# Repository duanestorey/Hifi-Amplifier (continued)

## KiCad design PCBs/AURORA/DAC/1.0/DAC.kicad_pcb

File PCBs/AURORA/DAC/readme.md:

## DAC 

### Version History

- 1.0: Initial Release

## #Speciality Components

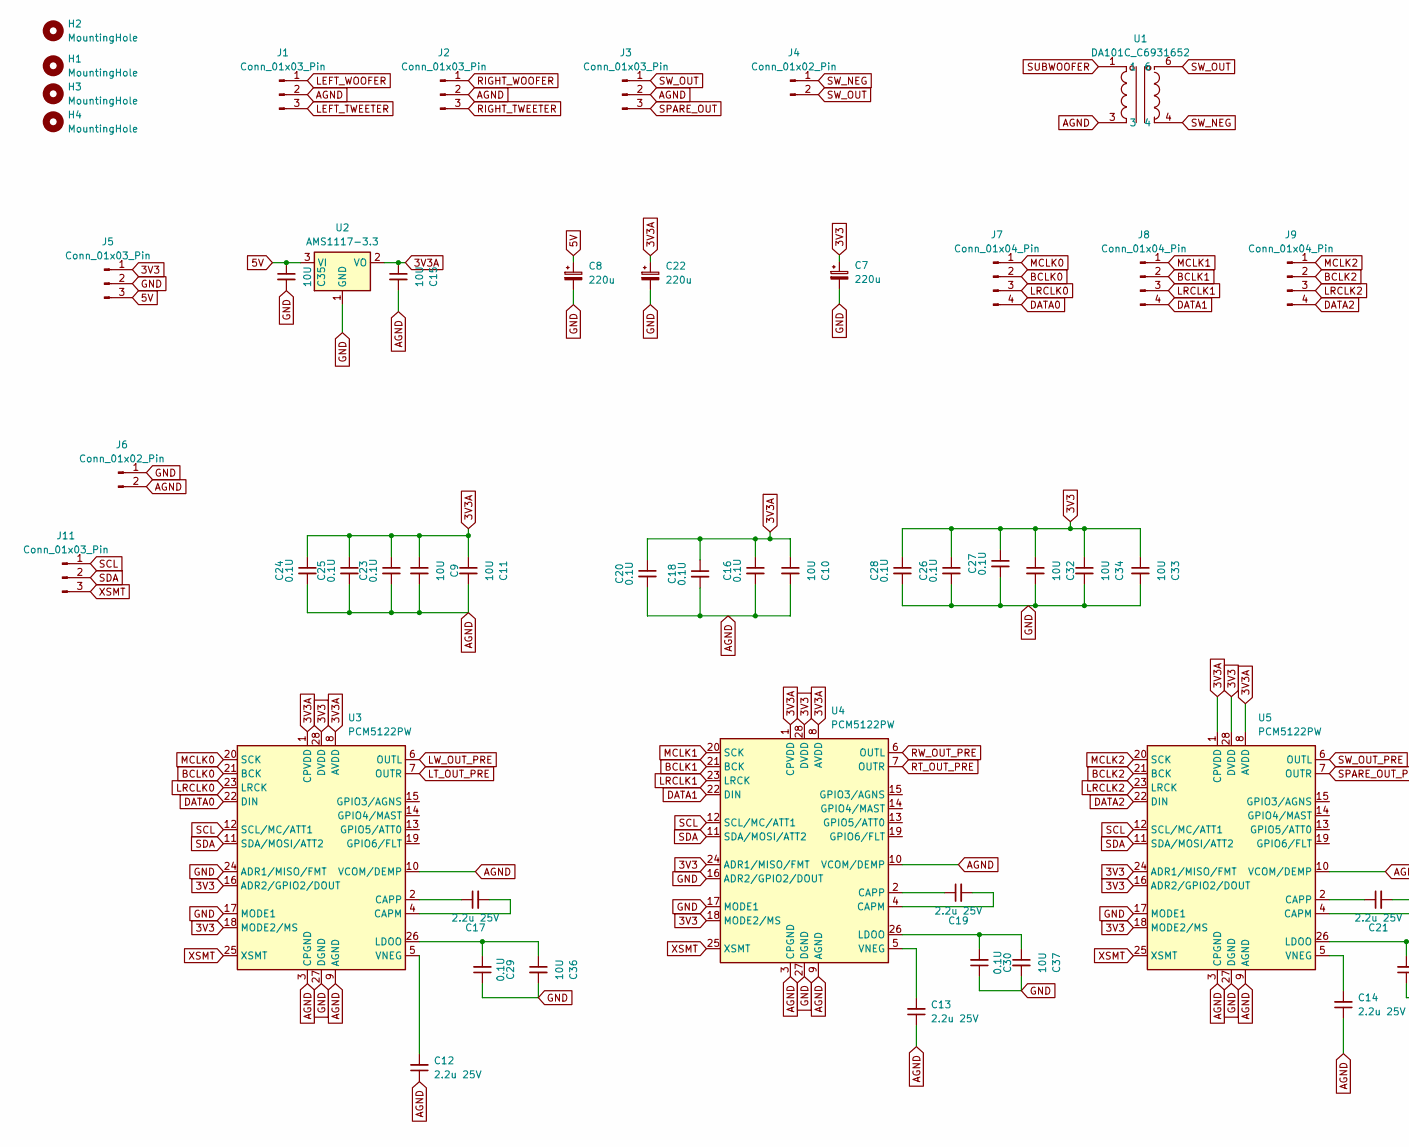
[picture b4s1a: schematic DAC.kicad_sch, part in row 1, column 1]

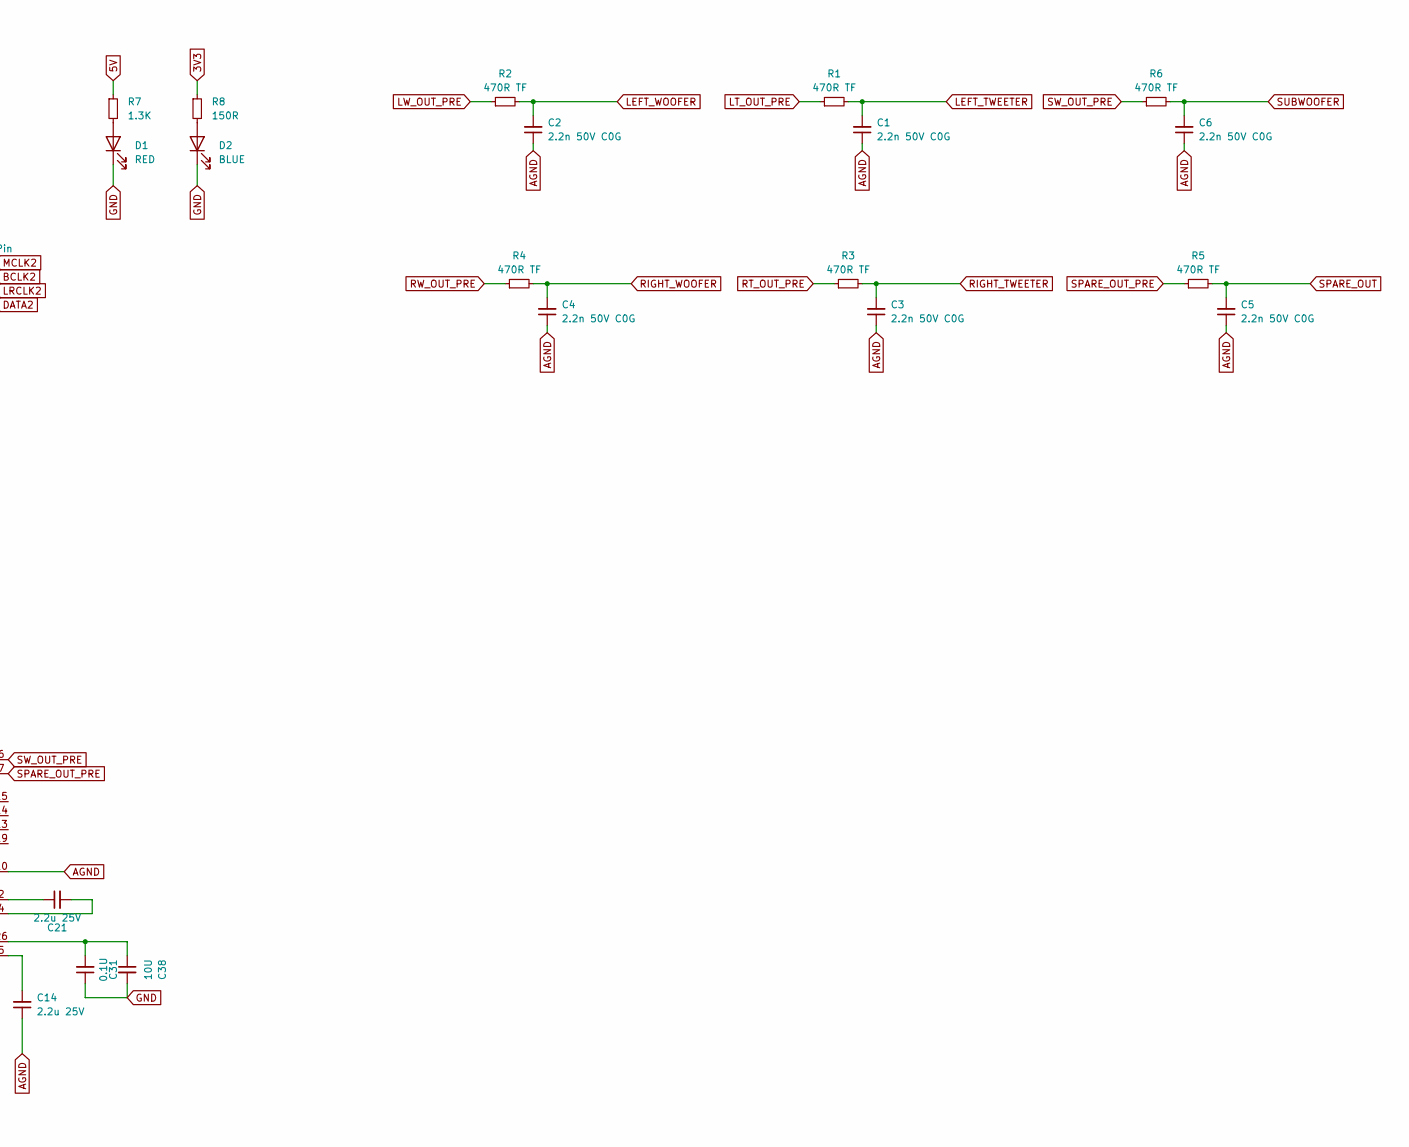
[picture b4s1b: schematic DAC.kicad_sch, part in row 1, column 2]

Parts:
C1, C2, C3, C4: 2.2n 50V C0G; C_0805_2012Metric_Pad1.18x1.45mm_HandSolder; Mouser 791-0805N222F500CT
C5, C6: 2.2n 50V C0G; C_0805_2012Metric_Pad1.18x1.45mm_HandSolder
C7, C8, C22: 220u; CP_Radial_D6.3mm_P2.50mm
C9, C10, C11, C15, C32, C33, C34, C35, C36, C37, C38: 10U; C_1206_3216Metric_Pad1.33x1.80mm_HandSolder
C12, C13, C14: 2.2u 25V; C_1206_3216Metric_Pad1.33x1.80mm_HandSolder
C16, C18, C20, C23, C24, C25, C26, C27, C28, C29, C30, C31: 0.1U; C_0805_2012Metric_Pad1.18x1.45mm_HandSolder
C17, C19, C21: 2.2u 25V; C_0805_2012Metric_Pad1.18x1.45mm_HandSolder
D1: RED; LED_0603_1608Metric
D2: BLUE; LED_0603_1608Metric
H1, H2, H3, H4: MountingHole; MountingHole_3.2mm_M3_DIN965_Pad_TopOnly
J1, J2, J3, J5, J11: Conn_01x03_Pin; JST_PH_B3B-PH-K_1x03_P2.00mm_Vertical
J4: Conn_01x02_Pin; JST_PH_B2B-PH-K_1x02_P2.00mm_Vertical
J6: Conn_01x02_Pin; PinHeader_1x02_P2.54mm_Vertical
J7, J8, J9: Conn_01x04_Pin; JST_PH_B4B-PH-K_1x04_P2.00mm_Vertical
R1, R2, R3, R4, R5, R6: 470R TF; R_0805_2012Metric_Pad1.20x1.40mm_HandSolder; Mouser 603-RT0805FRE07470RL
R7: 1.3K; R_0603_1608Metric_Pad0.98x0.95mm_HandSolder
R8: 150R; R_0603_1608Metric_Pad0.98x0.95mm_HandSolder
U1: DA101C_C6931652; XFMR-TH_4P-L9.5-W9.0-P5.08-LS10.2_C9900096976; LCSC Part C6931652
U2: AMS1117-3.3; SOT-223-3_TabPin2
U3, U4, U5: PCM5122PW; TSSOP-28_4.4x9.7mm_P0.65mm; Mouser 595-PCM5142PWR

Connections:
3V3: C7.1, C26.1, C27.1, C28.1, C32.1, C33.1, C34.1, J5.1, R8.1, U3.16 (ADR2/GPIO2/DOUT), U3.18 (MODE2/MS), U3.28 (DVDD), U4.18 (MODE2/MS), U4.24 (ADR1/MISO/FMT), U4.28 (DVDD), U5.16 (ADR2/GPIO2/DOUT), U5.18 (MODE2/MS), U5.24 (ADR1/MISO/FMT), U5.28 (DVDD)
3V3A: C9.1, C10.1, C11.1, C15.1, C16.1, C18.1, C20.1, C22.1, C23.1, C24.1, C25.1, U2.2 (VO), U3.1 (CPVDD), U3.8 (AVDD), U4.1 (CPVDD), U4.8 (AVDD), U5.1 (CPVDD), U5.8 (AVDD)
5V: C8.1, C35.1, J5.3, R7.1, U2.3 (VI)
AGND: C1.1, C2.1, C3.1, C4.1, C5.1, C6.1, C9.2, C10.2, C11.2, C12.1, C13.1, C14.1, C15.2, C16.2, C18.2, C20.2, C23.2, C24.2, C25.2, J1.2, J2.2, J3.2, J6.2, U1.3, U3.3 (CPGND), U3.9 (AGND), U3.10 (VCOM/DEMP), U4.3 (CPGND), U4.9 (AGND), U4.10 (VCOM/DEMP), U5.3 (CPGND), U5.9 (AGND), U5.10 (VCOM/DEMP)
BCLK0: J7.2, U3.21 (BCK)
BCLK1: J8.2, U4.21 (BCK)
BCLK2: J9.2, U5.21 (BCK)
DATA0: J7.4, U3.22 (DIN)
DATA1: J8.4, U4.22 (DIN)
DATA2: J9.4, U5.22 (DIN)
GND: C7.2, C8.2, C22.2, C26.2, C27.2, C28.2, C29.1, C30.1, C31.1, C32.2, C33.2, C34.2, C35.2, C36.2, C37.2, C38.2, D1.1 (K), D2.1 (K), J5.2, J6.1, U2.1 (GND), U3.17 (MODE1), U3.24 (ADR1/MISO/FMT), U3.27 (DGND), U4.16 (ADR2/GPIO2/DOUT), U4.17 (MODE1), U4.27 (DGND), U5.17 (MODE1), U5.27 (DGND)
LEFT_TWEETER: C1.2, J1.3, R1.2
LEFT_WOOFER: C2.2, J1.1, R2.2
LRCLK0: J7.3, U3.23 (LRCK)
LRCLK1: J8.3, U4.23 (LRCK)
LRCLK2: J9.3, U5.23 (LRCK)
LT_OUT_PRE: R1.1, U3.7 (OUTR)
LW_OUT_PRE: R2.1, U3.6 (OUTL)
MCLK0: J7.1, U3.20 (SCK)
MCLK1: J8.1, U4.20 (SCK)
MCLK2: J9.1, U5.20 (SCK)
unnamed: D1.2 (A), R7.2
unnamed: D2.2 (A), R8.2
unnamed: C17.2, U3.4 (CAPM)
unnamed: C17.1, U3.2 (CAPP)
unnamed: C29.2, C36.1, U3.26 (LDOO)
unnamed: C12.2, U3.5 (VNEG)
unnamed: C19.2, U4.4 (CAPM)
unnamed: C19.1, U4.2 (CAPP)
unnamed: C30.2, C37.1, U4.26 (LDOO)
unnamed: C13.2, U4.5 (VNEG)
unnamed: C21.2, U5.4 (CAPM)
unnamed: C21.1, U5.2 (CAPP)
unnamed: C31.2, C38.1, U5.26 (LDOO)
unnamed: C14.2, U5.5 (VNEG)
RIGHT_TWEETER: C3.2, J2.3, R3.2
RIGHT_WOOFER: C4.2, J2.1, R4.2
RT_OUT_PRE: R3.1, U4.7 (OUTR)
RW_OUT_PRE: R4.1, U4.6 (OUTL)
SCL: J11.1, U3.12 (SCL/MC/ATT1), U4.12 (SCL/MC/ATT1), U5.12 (SCL/MC/ATT1)
SDA: J11.2, U3.11 (SDA/MOSI/ATT2), U4.11 (SDA/MOSI/ATT2), U5.11 (SDA/MOSI/ATT2)
SPARE_OUT: C5.2, J3.3, R5.2
SPARE_OUT_PRE: R5.1, U5.7 (OUTR)
SUBWOOFER: C6.2, R6.2, U1.1
SW_NEG: J4.1, U1.4
SW_OUT: J3.1, J4.2, U1.6
SW_OUT_PRE: R6.1, U5.6 (OUTL)
XSMT: J11.3, U3.25 (XSMT), U4.25 (XSMT), U5.25 (XSMT)

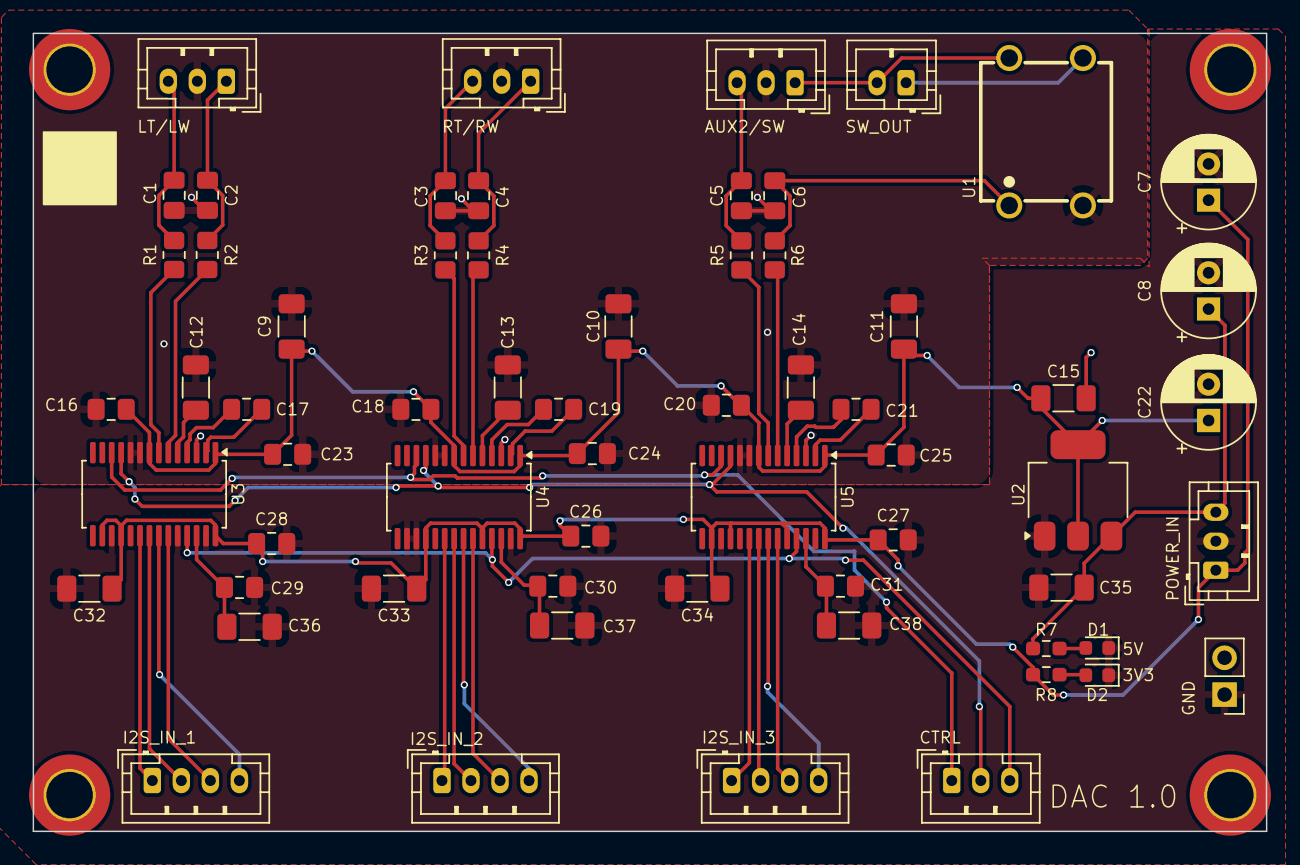
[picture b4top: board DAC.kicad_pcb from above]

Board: 2 copper layers, 85.0 x 55.0 mm, 67 parts (0 on the bottom side), 48 nets.

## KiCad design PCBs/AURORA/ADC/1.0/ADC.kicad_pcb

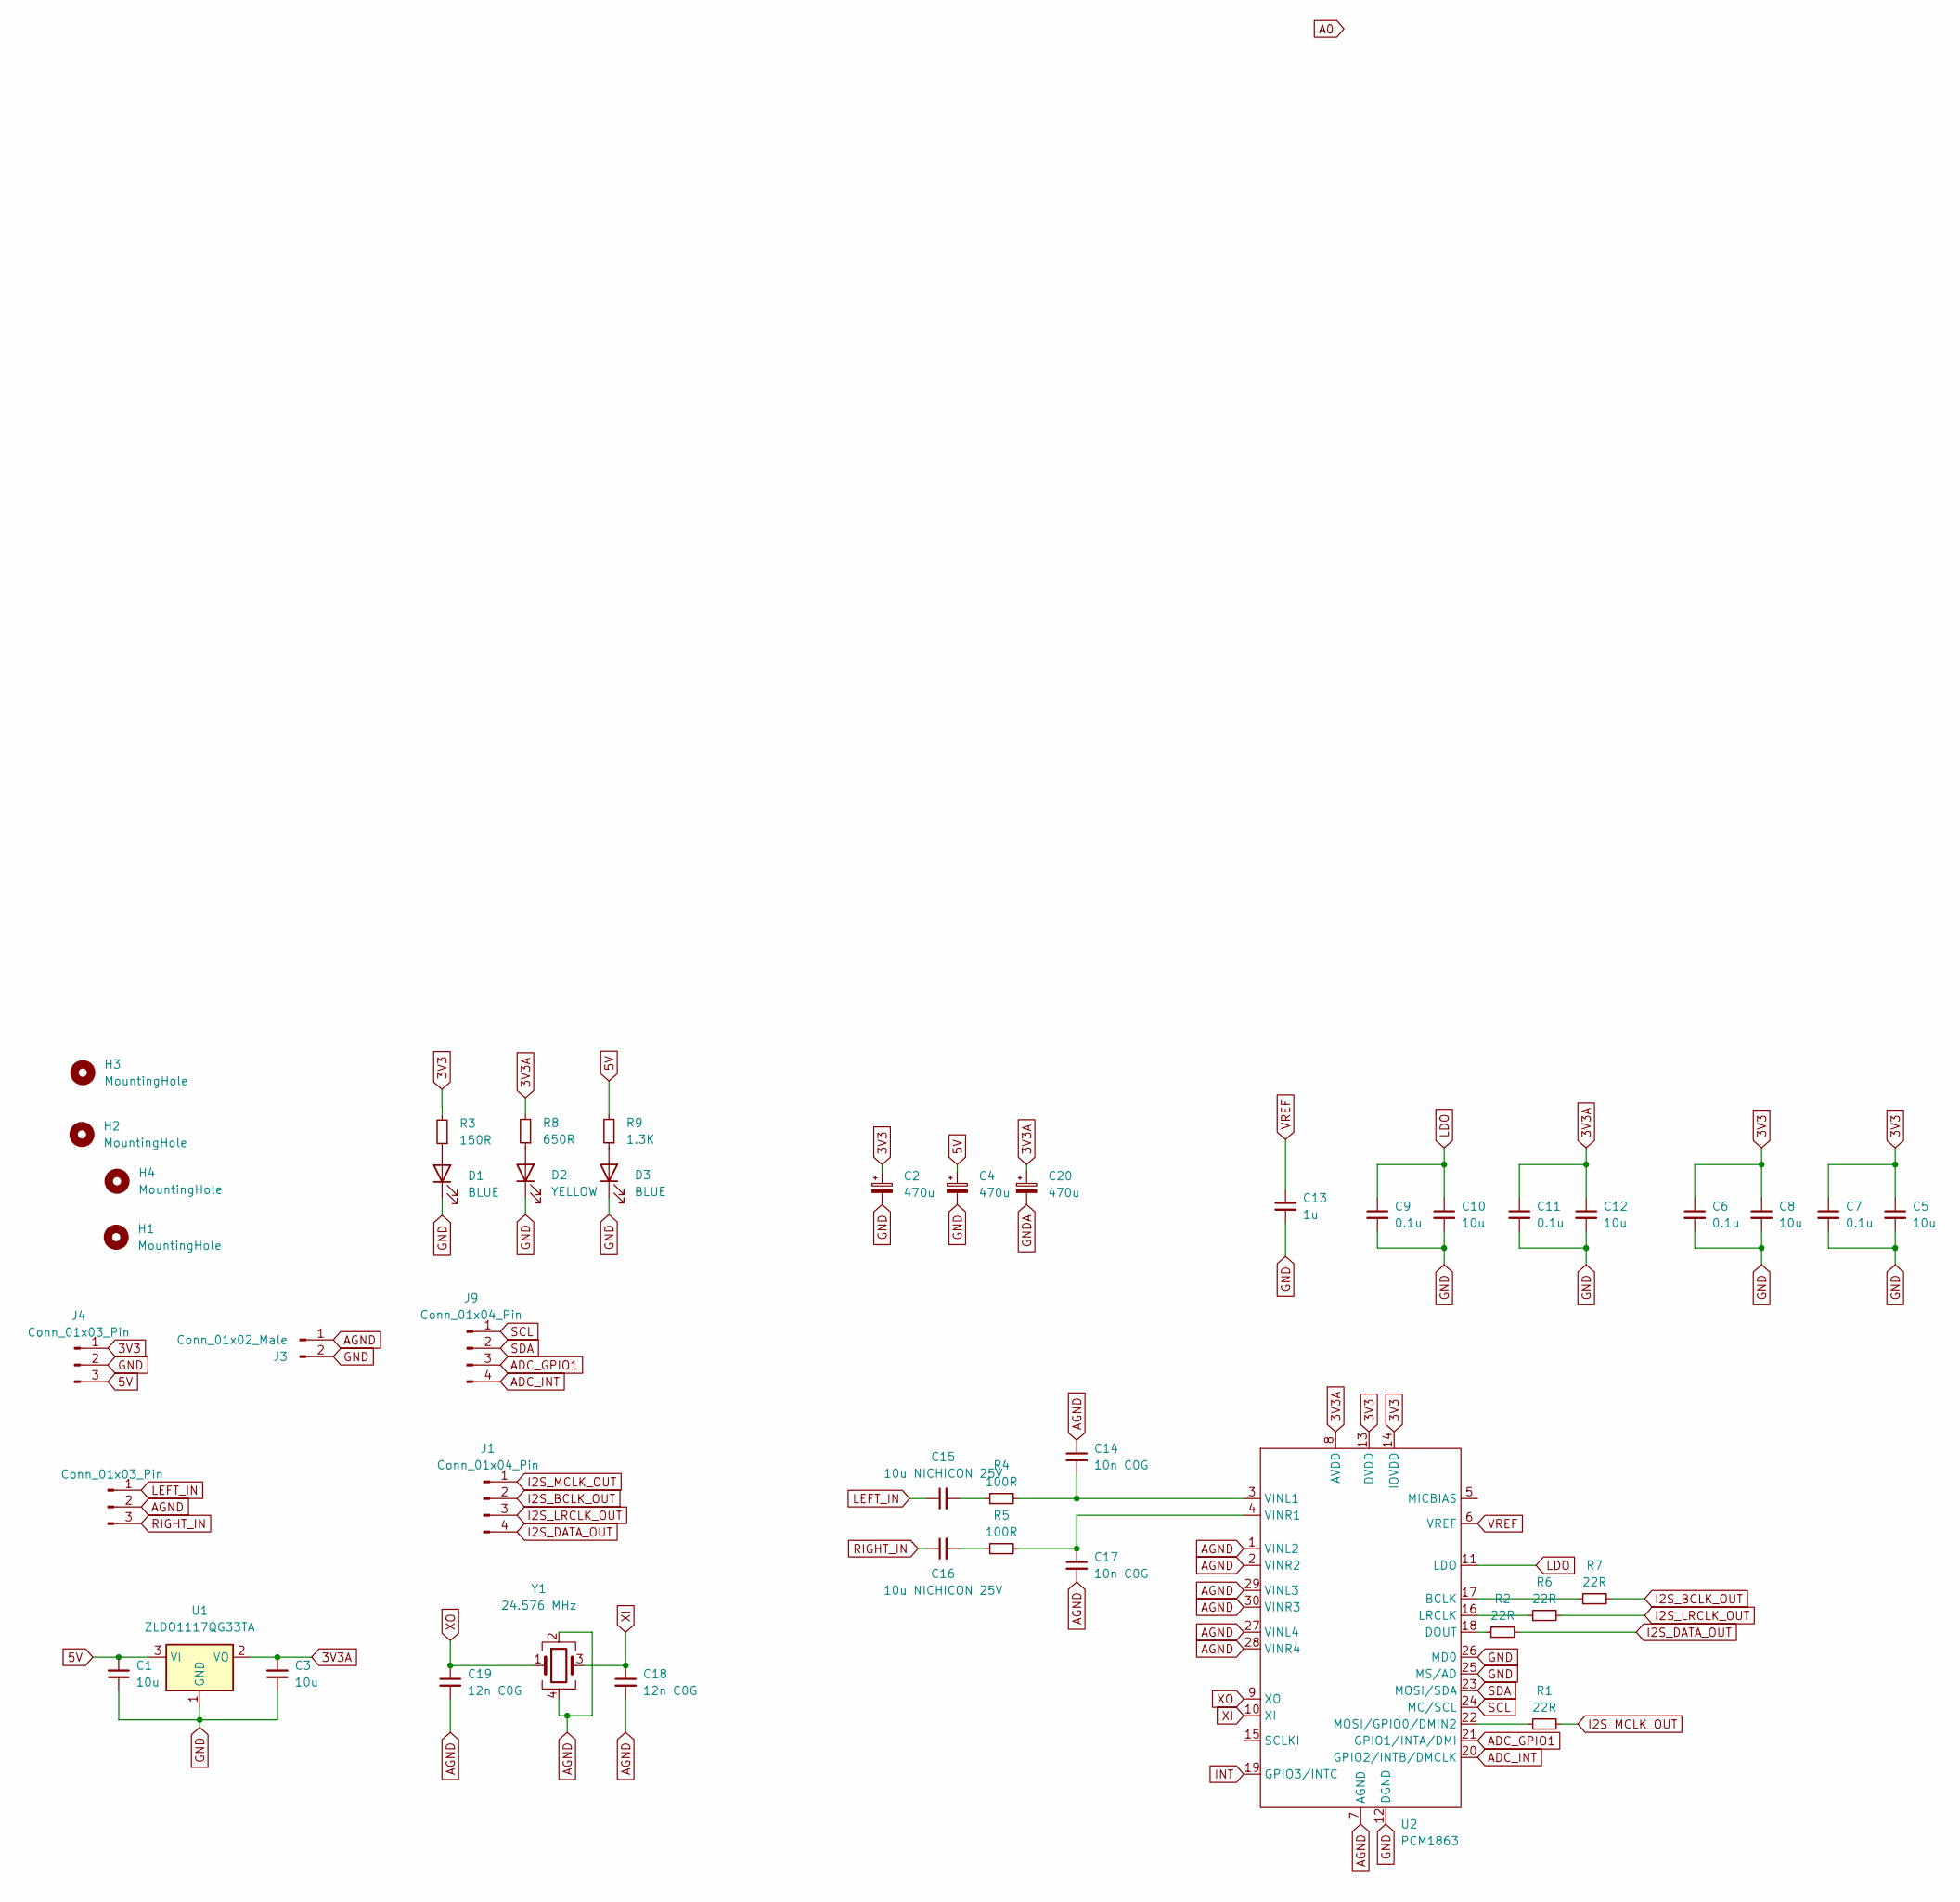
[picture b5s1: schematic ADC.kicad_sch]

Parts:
C1, C3, C5, C8, C10, C12: 10u; C_1206_3216Metric_Pad1.33x1.80mm_HandSolder
C2, C4, C20: 470u; CP_Radial_D6.3mm_P2.50mm
C6, C7, C9, C11: 0.1u; C_0805_2012Metric_Pad1.18x1.45mm_HandSolder
C13: 1u; C_1206_3216Metric_Pad1.33x1.80mm_HandSolder
C14, C17: 10n C0G; C_0805_2012Metric_Pad1.18x1.45mm_HandSolder; Mouser 791-0805N103G250CT
C15, C16: 10u NICHICON 25V; CP_Radial_D5.0mm_P2.00mm
C18, C19: 12n C0G; C_0805_2012Metric_Pad1.18x1.45mm_HandSolder; Mouser 791-0805N103G250CT
D1, D3: BLUE; LED_0603_1608Metric
D2: YELLOW; LED_0603_1608Metric
H1, H2, H3, H4: MountingHole; MountingHole_3.2mm_M3_DIN965_Pad_TopOnly
J1, J9: Conn_01x04_Pin; JST_PH_B4B-PH-K_1x04_P2.00mm_Vertical
J3: Conn_01x02_Male; PinHeader_1x02_P2.54mm_Vertical
J4, J5: Conn_01x03_Pin; JST_PH_B3B-PH-K_1x03_P2.00mm_Vertical
R1, R2, R6, R7: 22R; R_0805_2012Metric_Pad1.20x1.40mm_HandSolder; Mouser 603-RT0805FRE0722RL
R3: 150R; R_0603_1608Metric_Pad0.98x0.95mm_HandSolder
R4, R5: 100R; R_0805_2012Metric_Pad1.20x1.40mm_HandSolder; Mouser 603-RT0805FRE13100RL
R8: 650R; R_0603_1608Metric_Pad0.98x0.95mm_HandSolder
R9: 1.3K; R_0603_1608Metric_Pad0.98x0.95mm_HandSolder
U1: ZLDO1117QG33TA; SOT-223-3_TabPin2
U2: PCM1863; TSSOP-30_4.4x7.8mm_P0.5mm; Mouser 595-PCM1863DBT
U3: (no value)
Y1: 24.576 MHz; Crystal_SMD_3225-4Pin_3.2x2.5mm

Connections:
3V3: C2.1, C5.1, C6.1, C7.1, C8.1, J4.1, R3.2, U2.13 (DVDD), U2.14 (IOVDD)
3V3A: C3.2, C11.1, C12.1, C20.1, R8.2, U1.2 (VO), U2.8 (AVDD)
5V: C1.2, C4.1, J4.3, R9.2, U1.3 (VI)
ADC_GPIO1: J9.3, U2.21 (GPIO1/INTA/DMI)
ADC_INT: J9.4, U2.20 (GPIO2/INTB/DMCLK)
AGND: C14.1, C17.2, C18.2, C19.2, J3.1, J5.2, U2.1 (VINL2), U2.2 (VINR2), U2.7 (AGND), U2.27 (VINL4), U2.28 (VINR4), U2.29 (VINL3), U2.30 (VINR3), Y1.2, Y1.4
GND: C1.1, C2.2, C3.1, C4.2, C5.2, C6.2, C7.2, C8.2, C9.2, C10.2, C11.2, C12.2, C13.2, D1.1 (K), D2.1 (K), D3.1 (K), J3.2, J4.2, U1.1 (GND), U2.12 (DGND), U2.25 (MS/AD), U2.26 (MD0)
GNDA: C20.2
I2S_BCLK_OUT: J1.2, R7.2
I2S_DATA_OUT: J1.4, R2.2
I2S_LRCLK_OUT: J1.3, R6.2
I2S_MCLK_OUT: J1.1, R1.2
INT: U2.19 (GPIO3/INTC)
LDO: C9.1, C10.1, U2.11 (LDO)
LEFT_IN: C15.1, J5.1
unnamed: C15.2, R4.1
unnamed: C16.2, R5.1
unnamed: D1.2 (A), R3.1
unnamed: D2.2 (A), R8.1
unnamed: D3.2 (A), R9.1
unnamed: R7.1, U2.17 (BCLK)
unnamed: R2.1, U2.18 (DOUT)
unnamed: R6.1, U2.16 (LRCLK)
unnamed: R1.1, U2.22 (MOSI/GPIO0/DMIN2)
unnamed: C14.2, R4.2, U2.3 (VINL1)
unnamed: C17.1, R5.2, U2.4 (VINR1)
RIGHT_IN: C16.1, J5.3
SCL: J9.1, U2.24 (MC/SCL)
SDA: J9.2, U2.23 (MOSI/SDA)
VREF: C13.1, U2.6 (VREF)
XI: C18.1, U2.10 (XI), Y1.3
XO: C19.1, U2.9 (XO), Y1.1

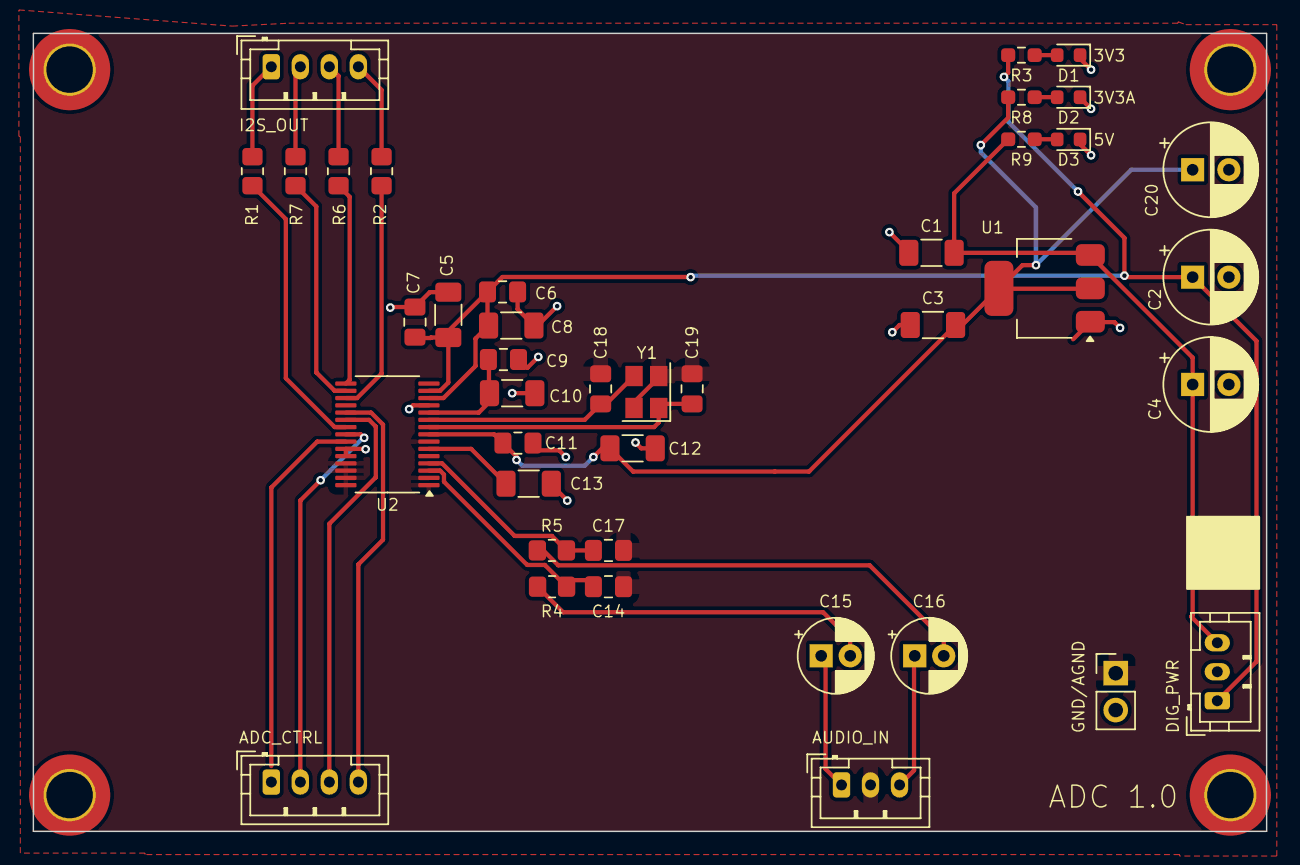
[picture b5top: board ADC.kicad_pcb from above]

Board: 2 copper layers, 85.0 x 55.0 mm, 44 parts (0 on the bottom side), 30 nets.

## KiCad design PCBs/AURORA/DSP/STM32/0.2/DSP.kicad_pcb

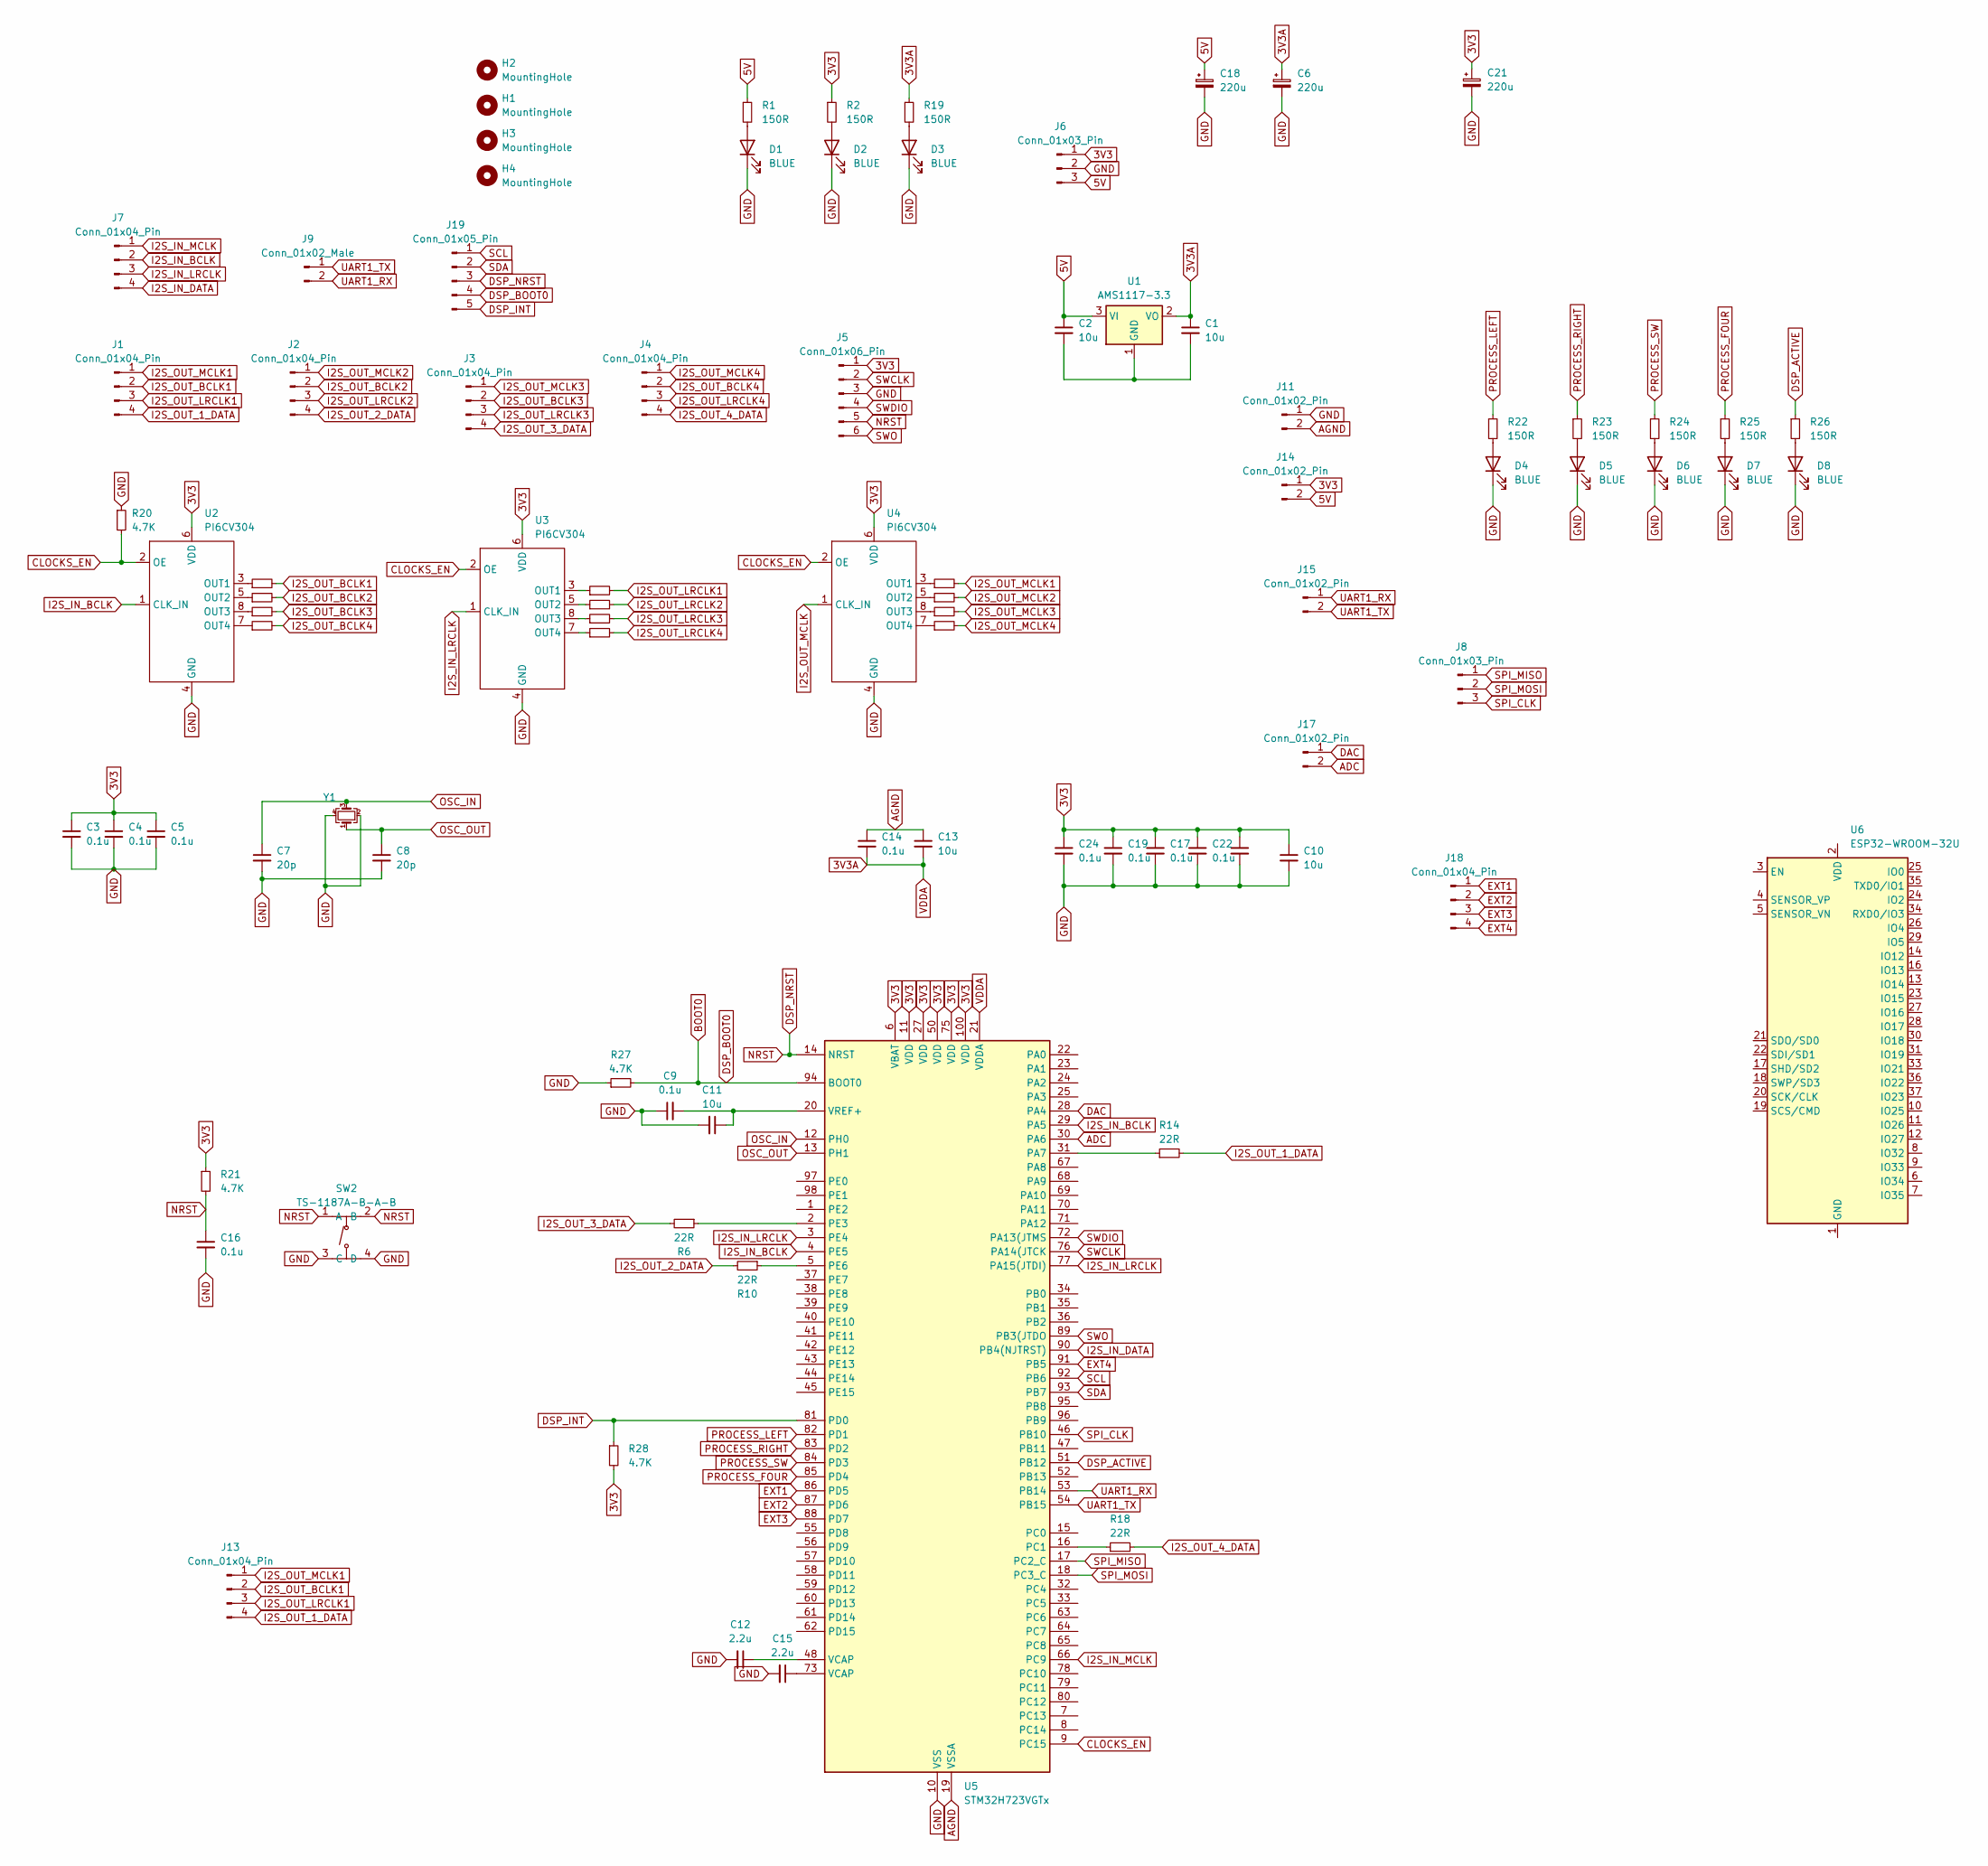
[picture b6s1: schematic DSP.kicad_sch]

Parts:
C1, C2, C10, C11, C13: 10u; C_1206_3216Metric; LCSC C13585
C3, C4, C5, C9, C14, C16, C17, C19, C22, C24, C29: 0.1u; C_0805_2012Metric; LCSC C28233
C6, C18, C21: 220u; CP_Elec_6.3x7.7; LCSC C4747974
C7, C8: 20p; C_0805_2012Metric; LCSC C1798
C12, C15: 2.2u; C_1206_3216Metric; LCSC C50254
D1, D2, D3, D4, D5, D6, D7, D8: BLUE; D_0603_1608Metric; LCSC C84259
H1, H2, H3, H4: MountingHole; MountingHole_3.2mm_M3_DIN965_Pad_TopOnly
J1, J2, J3, J4, J7: Conn_01x04_Pin; JST_PH_B4B-PH-K_1x04_P2.00mm_Vertical
J5: Conn_01x06_Pin; PinHeader_1x06_P2.54mm_Vertical; LCSC C6332199
J6: Conn_01x03_Pin; JST_PH_B3B-PH-K_1x03_P2.00mm_Vertical
J8: Conn_01x03_Pin; PinHeader_1x03_P2.54mm_Vertical
J9: Conn_01x02_Male; JST_PH_B2B-PH-K_1x02_P2.00mm_Vertical
J11, J14, J15, J17: Conn_01x02_Pin; PinHeader_1x02_P2.54mm_Vertical; LCSC C225477
J13, J18: Conn_01x04_Pin; PinHeader_1x04_P2.54mm_Vertical; LCSC C6332197
J19: Conn_01x05_Pin; JST_PH_B5B-PH-K_1x05_P2.00mm_Vertical
R1, R2, R19, R22, R23, R24, R25, R26: 150R; R_0603_1608Metric; LCSC C22808
R3, R4, R5, R6, R7, R8, R9, R10, R11, R12, R13, R14, R15, R16, R17, R18: 22R; R_0603_1608Metric; LCSC C23345
R20, R21, R27, R28: 4.7K; R_0603_1608Metric; LCSC C23162
SW2: TS-1187A-B-A-B; SW-SMD_4P-L5.1-W5.1-P3.70-LS6.5-TL_H1.5; LCSC Part C318884
U1: AMS1117-3.3; SOT-223-3_TabPin2; LCSC C6186
U2, U3, U4: PI6CV304; TSSOP-8_4.4x3mm_P0.65mm; Mouser 729-PI6CV304LEX
U5: STM32H723VGTx; LQFP-100_14x14mm_P0.5mm; LCSC C730142
U6: ESP32-WROOM-32U
Y1: 25 MHz; Crystal_SMD_SeikoEpson_FA238-4Pin_3.2x2.5mm; Mouser 520-240-8-33B2CKMTR3

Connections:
3V3: C3.1, C4.1, C5.1, C10.1, C17.1, C19.1, C21.1, C22.1, C24.1, C29.1, J5.1, J6.1, J14.1, R2.1, R21.1, R28.2, U2.6 (VDD), U3.6 (VDD), U4.6 (VDD), U5.6 (VBAT), U5.11 (VDD), U5.27 (VDD), U5.50 (VDD), U5.75 (VDD), U5.100 (VDD)
3V3A: C1.1, C6.1, C13.2, C14.2, R19.1, U1.2 (VO), U5.21 (VDDA)
5V: C2.1, C18.1, J6.3, J14.2, R1.1, U1.3 (VI)
ADC: J17.2, U5.30 (PA6)
AGND: C13.1, C14.1, J11.2, U5.19 (VSSA)
BOOT0: J19.4, R27.2, U5.94 (BOOT0)
CLOCKS_EN: R20.2, U2.2 (OE), U3.2 (OE), U4.2 (OE), U5.9 (PC15)
DAC: J17.1, U5.28 (PA4)
DSP_ACTIVE: R26.1, U5.51 (PB12)
DSP_INT: J19.5, R28.1, U5.81 (PD0)
DSP_NRST: C16.1, J5.5, J19.3, R21.2, SW2.1 (A), SW2.2 (B), U5.14 (NRST)
EXT1: J18.1, U5.86 (PD5)
EXT2: J18.2, U5.87 (PD6)
EXT3: J18.3, U5.88 (PD7)
EXT4: J18.4, U5.91 (PB5)
GND: C3.2, C4.2, C5.2, C6.2, C7.2, C8.2, C9.1, C10.2, C11.2, C12.2, C15.2, C16.2, C17.2, C18.2, C19.2, C21.2, C22.2, C24.2, C29.2, D1.1 (K), D2.1 (K), D3.1 (K), D4.1 (K), D5.1 (K), D6.1 (K), D7.1 (K), D8.1 (K), J5.3, J6.2, J11.1, R20.1, R27.1, SW2.3 (C), SW2.4 (D), U2.4 (GND), U3.4 (GND), U4.4 (GND), U5.10 (VSS), U5.26 (VSS), U5.49 (VSS), U5.74 (VSS), U5.99 (VSS), Y1.2, Y1.4
I2S_IN_BCLK: J7.2, U2.1 (CLK_IN), U5.4 (PE5), U5.29 (PA5)
I2S_IN_DATA: J7.4, U5.90 (PB4(NJTRST))
I2S_IN_LRCLK: J7.3, U3.1 (CLK_IN), U5.3 (PE4), U5.77 (PA15(JTDI))
I2S_IN_MCLK: J7.1, U5.66 (PC9)
I2S_OUT_1_DATA: J1.4, J13.4, R14.2
I2S_OUT_2_DATA: J2.4, R10.2
I2S_OUT_3_DATA: J3.4, R6.2
I2S_OUT_4_DATA: J4.4, R18.2
I2S_OUT_BCLK1: J1.2, J13.2, R4.2
I2S_OUT_BCLK2: J2.2, R8.2
I2S_OUT_BCLK3: J3.2, R12.2
I2S_OUT_BCLK4: J4.2, R16.2
I2S_OUT_LRCLK1: J1.3, J13.3, R5.2
I2S_OUT_LRCLK2: J2.3, R9.2
I2S_OUT_LRCLK3: J3.3, R13.2
I2S_OUT_LRCLK4: J4.3, R17.2
I2S_OUT_MCLK: U4.1 (CLK_IN)
I2S_OUT_MCLK1: J1.1, J13.1, R3.2
I2S_OUT_MCLK2: J2.1, R7.2
I2S_OUT_MCLK3: J3.1, R11.2
I2S_OUT_MCLK4: J4.1, R15.2
unnamed: C12.1, U5.48 (VCAP)
unnamed: C15.1, U5.73 (VCAP)
unnamed: D1.2 (A), R1.2
unnamed: D2.2 (A), R2.2
unnamed: D3.2 (A), R19.2
unnamed: D4.2 (A), R22.2
unnamed: D5.2 (A), R23.2
unnamed: D6.2 (A), R24.2
unnamed: D7.2 (A), R25.2
unnamed: D8.2 (A), R26.2
unnamed: C1.2, C2.2, U1.1 (GND)
unnamed: R4.1, U2.3 (OUT1)
unnamed: R8.1, U2.5 (OUT2)
unnamed: R12.1, U2.8 (OUT3)
unnamed: R16.1, U2.7 (OUT4)
unnamed: R5.1, U3.3 (OUT1)
unnamed: R9.1, U3.5 (OUT2)
unnamed: R13.1, U3.8 (OUT3)
unnamed: R17.1, U3.7 (OUT4)
unnamed: R3.1, U4.3 (OUT1)
unnamed: R7.1, U4.5 (OUT2)
unnamed: R11.1, U4.8 (OUT3)
unnamed: R15.1, U4.7 (OUT4)
unnamed: R14.1, U5.31 (PA7)
unnamed: R18.1, U5.16 (PC1)
unnamed: R6.1, U5.2 (PE3)
unnamed: R10.1, U5.5 (PE6)
unnamed: C9.2, C11.1, U5.20 (VREF+)
unnamed: U6.1 (GND), U6.15 (GND), U6.38 (GND), U6.39 (GND)
OSC_IN: C7.1, U5.12 (PH0), Y1.3
OSC_OUT: C8.1, U5.13 (PH1), Y1.1
PROCESS_FOUR: R25.1, U5.85 (PD4)
PROCESS_LEFT: R22.1, U5.82 (PD1)
PROCESS_RIGHT: R23.1, U5.83 (PD2)
PROCESS_SW: R24.1, U5.84 (PD3)
SCL: J19.1, U5.92 (PB6)
SDA: J19.2, U5.93 (PB7)
SPI_CLK: J8.3, U5.46 (PB10)
SPI_MISO: J8.1, U5.17 (PC2_C)
SPI_MOSI: J8.2, U5.18 (PC3_C)
SWCLK: J5.2, U5.76 (PA14(JTCK)
SWDIO: J5.4, U5.72 (PA13(JTMS)
SWO: J5.6, U5.89 (PB3(JTDO)
UART1_RX: J9.2, J15.1, U5.53 (PB14)
UART1_TX: J9.1, J15.2, U5.54 (PB15)
